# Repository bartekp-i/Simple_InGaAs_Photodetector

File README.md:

# Simple_InGaAs_Photodetector
This repository documents how the photodetector was built, starting from developing a electronic circuit and a PCB as well as assembly and tests (ongoing)
# 6 GHz InGaAs Photodetector PCB and schematics

## Technical Specifications

| Parameter | Specification |
| :--- | :--- |
| **RF Bandwidth** | DC up to 6 GHz |
| **Characteristic Impedance** | 50 Ω (Matched Coplanar Waveguide with Ground) |
| **Bias Voltage ($V_{CC}$)** | ~12 VDC (Nominal) |
| **RF Output Interface** | Edge-Launch SMA Connector |
| **Power Supply** | 3 LiPo 3.7V Batteries via 2x4 Pin Header |
| **Design Software** | KiCad v9.0

---

## System Architecture & Circuit Design

The circuit implements a high-bandwidth, low-noise reverse-biased InGaAs photodetector topology designed to extract fast electrical transients from optical signals.

### 1. Photodiode Biasing Topology (`PD1`)
The photodiode (`PD1`) is configured in a reverse-bias configuration:
* **Cathode (Pin 1):** Connected to the filtered +12V DC bias line.
* **Anode (Pin 2):** Connected directly to the 50 Ω RF transmission line leading to the SMA output.
* **Case(Pin 3):** Directly tied to Ground to provide structural shielding.

**Why:** Applying a +12V reverse bias across the photodiode significantly widens its internal depletion region. This minimizes the junction capacitance ($C_j$), which is the primary limiting factor for high-speed photodetector bandwidth. The electrical bandwidth is governed by:

$$f_{3\text{dB}} \approx \frac{1}{2\pi \cdot R_L \cdot C_j}$$

Where $R_L$ is the 50 Ω load resistor internal to the connected measurement equipment (e.g., oscilloscope or spectrum analyzer). Minimizing $C_j$ ensures crisp pulse responses and maximum frequency extension up to 6 GHz.

### 2. Multi-Tier Power Decoupling & Low-Pass Filter Network
To prevent high-frequency RF currents from leaking into the power supply rail and to insulate the photodiode from power supply ripple, an aggressive, multi-stage cascading low-pass filter is implemented:
* **Bulk Storage (`C1`, `C2`):** A **10 µF (`C1`)** and a **6.8 µF (`C2`)** capacitor flank a **1 kΩ (`R1`)** series isolation resistor. This network forms an RC low-pass filter ($f_c \approx 23.4\text{ Hz}$) that squashes low-frequency power supply noise and ripple.
* **RF Decoupling Array (`C3`, `C4`, `C5`):** Three ultra-low Equivalent Series Resistance (ESR) and Equivalent Series Inductance (ESL) surface-mount capacitors are placed in parallel directly adjacent to the photodiode cathode: **47 pF (`C3`)**, **10 pF (`C4`)**, and **2 pF (`C5`)**. 

*Why:** Single capacitors possess self-resonant frequencies (SRF) above which they behave inductively. By staggering capacitance values down to 2 pF, the board maintains a broad, ultra-low impedance return path to ground across the entire multi-gigahertz spectrum, ensuring the photodiode sees a perfectly stable, noise-free DC bias.

---

## PCB Design & RF Considerations

At 6 GHz, electrical traces cannot be treated as simple lumped-element wires; they must be managed as **distributed-element transmission lines**. 

### 1. 50 Ω Impedance-Matched Transmission Line
The RF signal path connecting the photodiode anode to the SMA connector uses a **Coplanar Waveguide with Ground (CPWG)** geometry. 
* **Geometry:** A central signal trace surrounded on the same layer by continuous ground planes, separated by a precise air gap (0.3mm from each side), with a solid reference ground plane on the layer directly below.
* **Impedance Target:** Exactly **50 Ω** at 6 GHz. Trace width carefully designed since trace length needed to be more than λ/10 due to mechanical constraints.
* **Design Execution:** The width of the central trace and the width of the ground clearances are precisely computed based on the PCB stackup's dielectric constant ($\epsilon_r$), substrate height (FR4 or specialized high-frequency laminate), and copper thickness. This precise geometric control prevents impedance discontinuities, minimizing signal reflections and return loss ($S_{11}$).

### 2. Via Fence & Stiching
The PCB layout features a highly dense matrix of ground via stitching:
* **Via Fencing:** Rows of closely spaced via stitches flank both sides of the CPWG transmission line. This bounds the electromagnetic fields within the dielectric, suppresses parasitic substrate modes, and prevents cross-coupling or radiation loss. The distance between each via and from the edge of the trace was carefully calculated and respectively equals, 2 mm and 1.95mm (measured from centre of the via to centre of the path)
* **Resonance Suppression:** The entire board area is stitched with vias to tightly couple all ground planes together. This eliminates structural ground loops and prevents the PCB substrate from acting as a resonant cavity at microwave frequencies.
* **Mounting Hole Shielding:** All 4 mechanical mounting holes are encircled by dense via rings, binding the chassis ground firmly to the internal layer grounds to eliminate localized electromagnetic radiation.

### 3. Component Layout & RF Footprints
* **Linear Signal Flow:** The design maintains a perfectly straight. Right-angle bends are entirely avoided, as they introduce parasitic capacitive columns that degrade high-frequency signals.
* **Decoupling Proximity:** The sub-nanofarad capacitors (`C3`, `C4`, `C5`) are placed immediately adjacent to the photodiode pins using minimal trace lengths to mitigate the parasitic trace inductance that would otherwise invalidate their high-frequency filtering performance.
* **Missing Solder Mask:**  Peeling back the mask, ensures that the 6 GHz signal experiences predictable 50 $\Omega$ impedance, minimal signal attenuation, and maximum propagation speed by utilizing air as the primary upper dielectric.

---

## Component Bill of Materials (BOM)

| Reference | Qty | Value | Package | Description |
| :--- | :--- | :--- | :--- | :--- |
| **PD1** | 1 | InGaAs Photodiode | 3-Pin Package | High-bandwidth Photodiode (6 GHz) |
| **J1** | 1 | CON-SMA-EDGE-SRP | Edge-Mount SMA | 50 Ω Female RF Edge-Launch Connector |
| **J2** | 1 | 2x4 Header (2.54mm) | Thru-Hole | Power/GND Distribution Interface |
| **R1** | 1 | 1 kΩ | SMD 0402/0201 | Thick/Thin Film Isolation Resistor |
| **C1** | 1 | 10 µF | SMD 0805/1206 | Ceramic Bulk Capacitor |
| **C2** | 1 | 6.8 µF | SMD 0805 | Ceramic Bulk Filter Capacitor |
| **C3** | 1 | 47 pF | SMD 0402/0201 | Ultra-Low ESR High-Q RF Capacitor |
| **C4** | 1 | 10 pF | SMD 0402/0201 | Ultra-Low ESR High-Q RF Capacitor |
| **C5** | 1 | 2 pF | SMD 0402/0201 | Ultra-Low ESR High-Q RF Capacitor |

## PCB and Schematic

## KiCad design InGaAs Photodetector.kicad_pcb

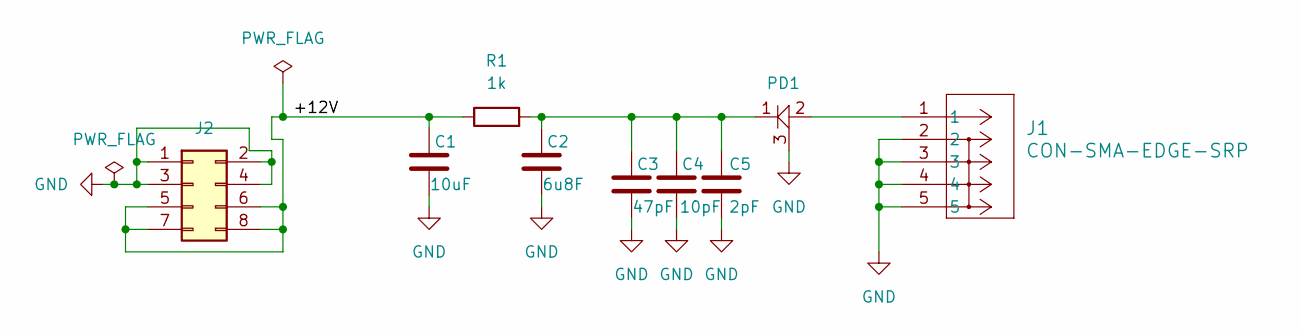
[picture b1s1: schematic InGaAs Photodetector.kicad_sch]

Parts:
C1: 10uF; C_0805_2012Metric
C2: 6u8F; C_0805_2012Metric
C3: 47pF; C_0402_1005Metric
C4: 2pF; C_0402_1005Metric
C5: 10pF; C_0402_1005Metric
J1: CON-SMA-EDGE-SRP; Untitled
J2: Conn_02x04_Odd_Even; heder2x4
PD1: Photodiode
R1: 1k; R_0402_1005Metric

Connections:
/+12V: C1.1, J2.5, J2.6, J2.7, J2.8, R1.1
GND: C1.2, C2.2, C3.2, C4.2, C5.2, J1.2, J1.3, J1.4, J1.5, J2.1, J2.2, J2.3, J2.4, PD1.3 (Case)
unnamed: J1.1, PD1.2 (Anode)
unnamed: C2.1, C3.1, C4.1, C5.1, PD1.1 (Cathode), R1.2

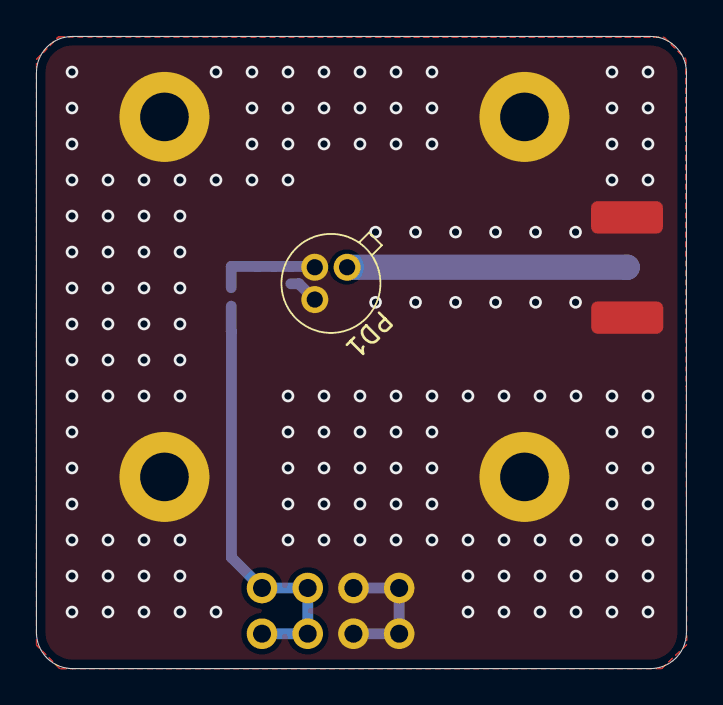
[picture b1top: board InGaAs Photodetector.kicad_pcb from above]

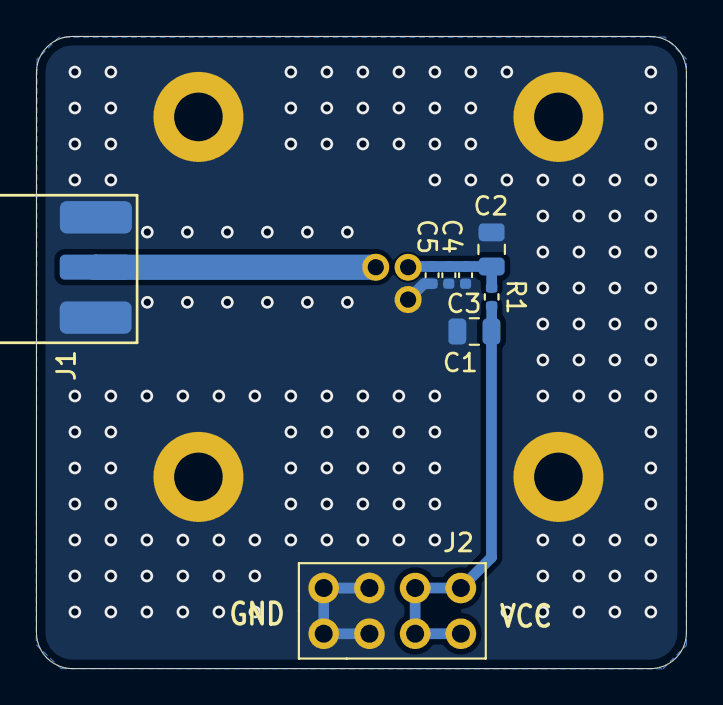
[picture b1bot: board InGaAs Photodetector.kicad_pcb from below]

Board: 2 copper layers, 36.1 x 35.1 mm, 9 parts (8 on the bottom side), 4 nets.

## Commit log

2026-05-28 Create test
